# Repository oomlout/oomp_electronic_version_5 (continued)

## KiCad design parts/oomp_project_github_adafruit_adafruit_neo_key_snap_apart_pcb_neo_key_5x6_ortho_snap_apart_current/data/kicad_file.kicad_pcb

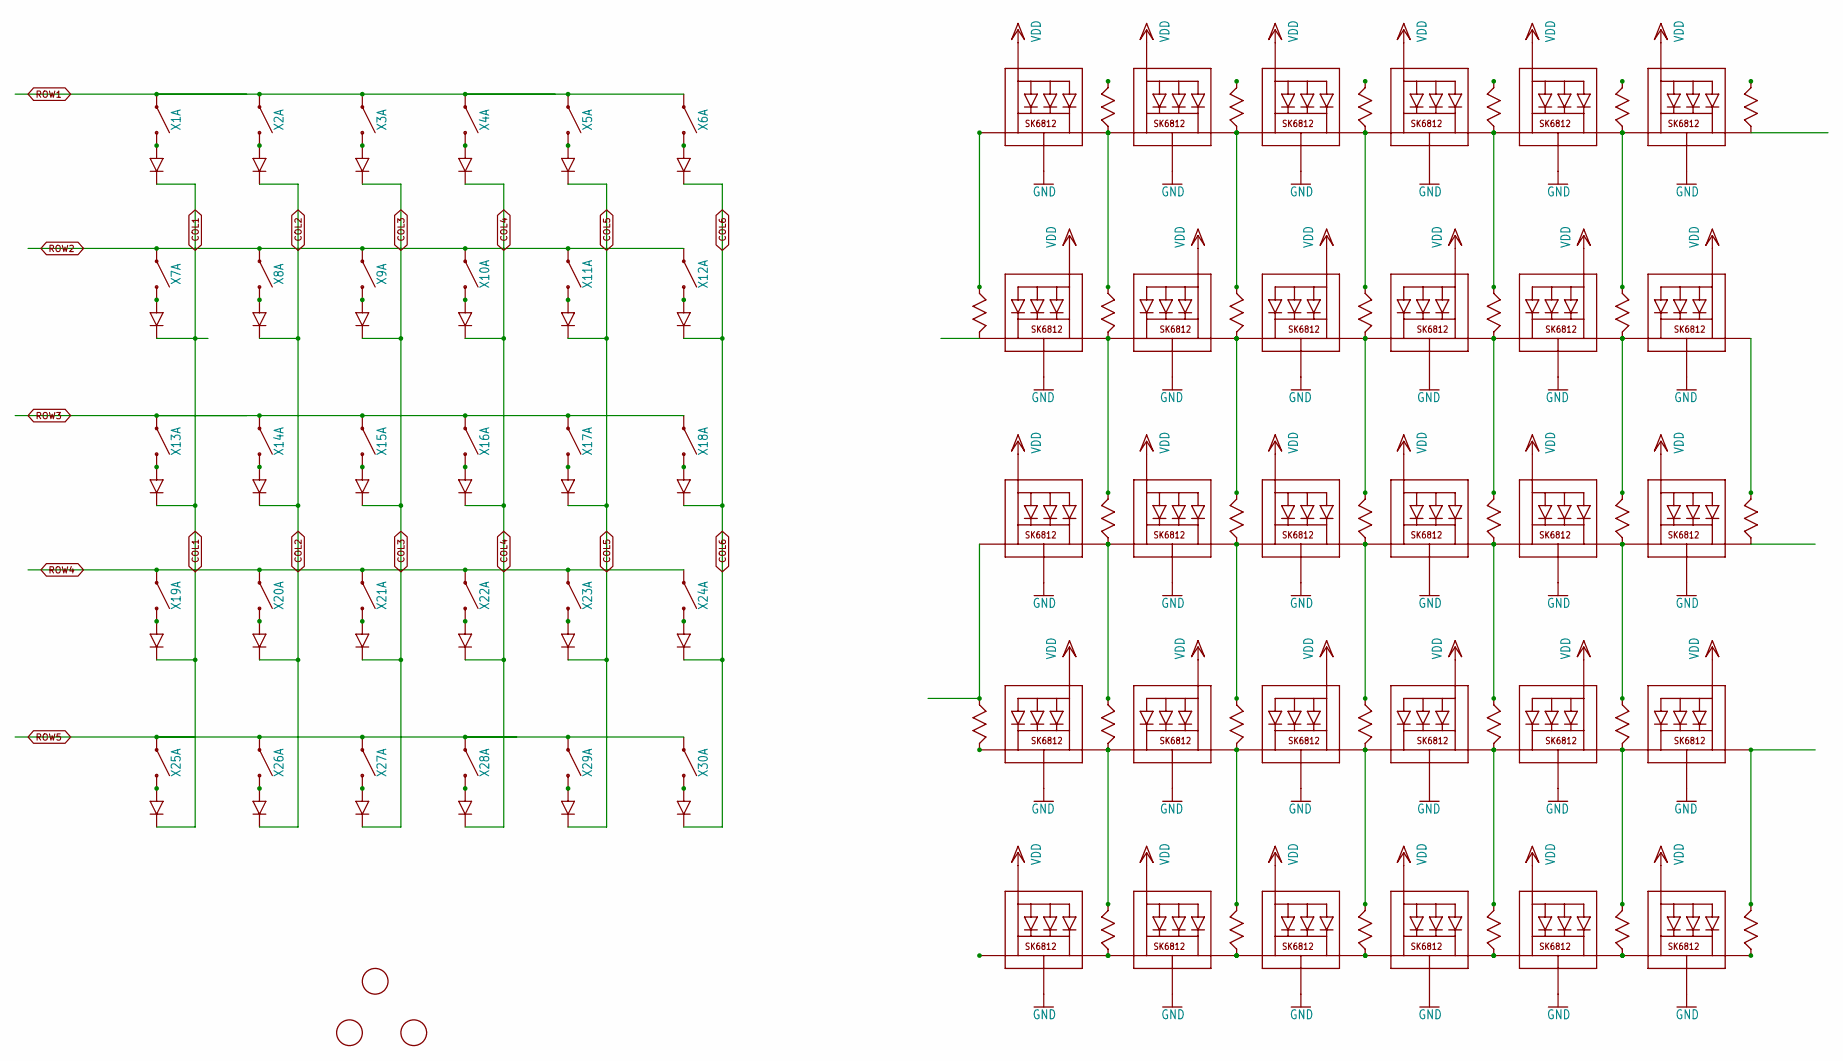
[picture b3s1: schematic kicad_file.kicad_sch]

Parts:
U$1, U$2, U$3: FIDUCIAL; FIDUCIAL_1MM
X1, X2, X3, X4, X5, X6, X13, X14, X15, X16, X17, X18, X25, X26, X27, X28, X29, X30: KAILH_SOCKET_TILE
X7, X8, X9, X10, X11, X12, X19, X20, X21, X22, X23, X24: KAILH_SOCKET_TILE_REVERSE; KAILH_SOCKET_TILE_REV

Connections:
COL1: X1.C (SW_C), X1.C1 (SW_C), X1.C2 (SW_C), X7.C (SW_C), X7.C1 (SW_C), X7.C2 (SW_C), X13.C (SW_C), X13.C1 (SW_C), X13.C2 (SW_C), X19.C (SW_C), X19.C1 (SW_C), X19.C2 (SW_C), X25.C (SW_C), X25.C1 (SW_C), X25.C2 (SW_C)
COL2: X2.C (SW_C), X2.C1 (SW_C), X2.C2 (SW_C), X8.C (SW_C), X8.C1 (SW_C), X8.C2 (SW_C), X14.C (SW_C), X14.C1 (SW_C), X14.C2 (SW_C), X20.C (SW_C), X20.C1 (SW_C), X20.C2 (SW_C), X26.C (SW_C), X26.C1 (SW_C), X26.C2 (SW_C)
COL3: X3.C (SW_C), X3.C1 (SW_C), X3.C2 (SW_C), X9.C (SW_C), X9.C1 (SW_C), X9.C2 (SW_C), X15.C (SW_C), X15.C1 (SW_C), X15.C2 (SW_C), X21.C (SW_C), X21.C1 (SW_C), X21.C2 (SW_C), X27.C (SW_C), X27.C1 (SW_C), X27.C2 (SW_C)
COL4: X4.C (SW_C), X4.C1 (SW_C), X4.C2 (SW_C), X10.C (SW_C), X10.C1 (SW_C), X10.C2 (SW_C), X16.C (SW_C), X16.C1 (SW_C), X16.C2 (SW_C), X22.C (SW_C), X22.C1 (SW_C), X22.C2 (SW_C), X28.C (SW_C), X28.C1 (SW_C), X28.C2 (SW_C)
COL5: X5.C (SW_C), X5.C1 (SW_C), X5.C2 (SW_C), X11.C (SW_C), X11.C1 (SW_C), X11.C2 (SW_C), X17.C (SW_C), X17.C1 (SW_C), X17.C2 (SW_C), X23.C (SW_C), X23.C1 (SW_C), X23.C2 (SW_C), X29.C (SW_C), X29.C1 (SW_C), X29.C2 (SW_C)
COL6: X6.C (SW_C), X6.C1 (SW_C), X6.C2 (SW_C), X12.C (SW_C), X12.C1 (SW_C), X12.C2 (SW_C), X18.C (SW_C), X18.C1 (SW_C), X18.C2 (SW_C), X24.C (SW_C), X24.C1 (SW_C), X24.C2 (SW_C), X30.C (SW_C), X30.C1 (SW_C), X30.C2 (SW_C)
GND: X1.3-GND (GND), X1.C- (GND), X1.GND1 (GND), X1.GND2 (GND), X2.3-GND (GND), X2.C- (GND), X2.GND1 (GND), X2.GND2 (GND), X3.3-GND (GND), X3.C- (GND), X3.GND1 (GND), X3.GND2 (GND), X4.3-GND (GND), X4.C- (GND), X4.GND1 (GND), X4.GND2 (GND), X5.3-GND (GND), X5.C- (GND), X5.GND1 (GND), X5.GND2 (GND), X6.3-GND (GND), X6.C- (GND), X6.GND1 (GND), X6.GND2 (GND), X7.3-GND (GND), X7.C- (GND), X7.GND1 (GND), X7.GND2 (GND), X8.3-GND (GND), X8.C- (GND), X8.GND1 (GND), X8.GND2 (GND), X9.3-GND (GND), X9.C- (GND), X9.GND1 (GND), X9.GND2 (GND), X10.3-GND (GND), X10.C- (GND), X10.GND1 (GND), X10.GND2 (GND), X11.3-GND (GND), X11.C- (GND), X11.GND1 (GND), X11.GND2 (GND), X12.3-GND (GND), X12.C- (GND), X12.GND1 (GND), X12.GND2 (GND), X13.3-GND (GND), X13.C- (GND), X13.GND1 (GND), X13.GND2 (GND), X14.3-GND (GND), X14.C- (GND), X14.GND1 (GND), X14.GND2 (GND), X15.3-GND (GND), X15.C- (GND), X15.GND1 (GND), X15.GND2 (GND), X16.3-GND (GND), X16.C- (GND), X16.GND1 (GND), X16.GND2 (GND), X17.3-GND (GND), X17.C- (GND), X17.GND1 (GND), X17.GND2 (GND), X18.3-GND (GND), X18.C- (GND), X18.GND1 (GND), X18.GND2 (GND), X19.3-GND (GND), X19.C- (GND), X19.GND1 (GND), X19.GND2 (GND), X20.3-GND (GND), X20.C- (GND), X20.GND1 (GND), X20.GND2 (GND), X21.3-GND (GND), X21.C- (GND), X21.GND1 (GND), X21.GND2 (GND), X22.3-GND (GND), X22.C- (GND), X22.GND1 (GND), X22.GND2 (GND), X23.3-GND (GND), X23.C- (GND), X23.GND1 (GND), X23.GND2 (GND), X24.3-GND (GND), X24.C- (GND), X24.GND1 (GND), X24.GND2 (GND), X25.3-GND (GND), X25.C- (GND), X25.GND1 (GND), X25.GND2 (GND), X26.3-GND (GND), X26.C- (GND), X26.GND1 (GND), X26.GND2 (GND), X27.3-GND (GND), X27.C- (GND), X27.GND1 (GND), X27.GND2 (GND), X28.3-GND (GND), X28.C- (GND), X28.GND1 (GND), X28.GND2 (GND), X29.3-GND (GND), X29.C- (GND), X29.GND1 (GND), X29.GND2 (GND), X30.3-GND (GND), X30.C- (GND), X30.GND1 (GND), X30.GND2 (GND)
unnamed: X1.4-DIN (DI), X1.DIN (DI), X1.DIN1 (DI), X2.2-DOUT (DO), X2.DOUT (DO), X2.DOUT1 (DO), X8.DIN_C (DI1), X8.DIN_C1 (DI1)
unnamed: X1.D+ (DA), X1.DA
unnamed: X1.DIN_C (DI1), X1.DIN_C1 (DI1)
unnamed: X2.D+ (DA), X2.DA
unnamed: X4.D+ (DA), X4.DA
unnamed: X1.2-DOUT (DO), X1.DOUT (DO), X1.DOUT1 (DO), X7.DIN_C (DI1), X7.DIN_C1 (DI1)
unnamed: X7.D+ (DA), X7.DA
unnamed: X2.DIN_C (DI1), X2.DIN_C1 (DI1)
unnamed: X3.D+ (DA), X3.DA
unnamed: X2.4-DIN (DI), X2.DIN (DI), X2.DIN1 (DI), X3.2-DOUT (DO), X3.DOUT (DO), X3.DOUT1 (DO), X9.DIN_C (DI1), X9.DIN_C1 (DI1)
unnamed: X3.4-DIN (DI), X3.DIN (DI), X3.DIN1 (DI), X4.2-DOUT (DO), X4.DOUT (DO), X4.DOUT1 (DO), X10.DIN_C (DI1), X10.DIN_C1 (DI1)
unnamed: X3.DIN_C (DI1), X3.DIN_C1 (DI1)
unnamed: X4.4-DIN (DI), X4.DIN (DI), X4.DIN1 (DI), X5.2-DOUT (DO), X5.DOUT (DO), X5.DOUT1 (DO), X11.DIN_C (DI1), X11.DIN_C1 (DI1)
unnamed: X4.DIN_C (DI1), X4.DIN_C1 (DI1)
unnamed: X6.D+ (DA), X6.DA
unnamed: X5.4-DIN (DI), X5.DIN (DI), X5.DIN1 (DI), X6.2-DOUT (DO), X6.DOUT (DO), X6.DOUT1 (DO), X12.DIN_C (DI1), X12.DIN_C1 (DI1)
unnamed: X12.2-DOUT (DO), X12.DOUT (DO), X12.DOUT1 (DO), X18.DIN_C (DI1), X18.DIN_C1 (DI1)
unnamed: X6.DIN_C (DI1), X6.DIN_C1 (DI1)
unnamed: X5.D+ (DA), X5.DA
unnamed: X5.DIN_C (DI1), X5.DIN_C1 (DI1)
unnamed: X6.4-DIN (DI), X6.DIN (DI), X6.DIN1 (DI)
unnamed: X13.D+ (DA), X13.DA
unnamed: X8.D+ (DA), X8.DA
unnamed: X8.2-DOUT (DO), X8.DOUT (DO), X8.DOUT1 (DO), X9.4-DIN (DI), X9.DIN (DI), X9.DIN1 (DI), X14.DIN_C (DI1), X14.DIN_C1 (DI1)
unnamed: X13.2-DOUT (DO), X13.DOUT (DO), X13.DOUT1 (DO), X19.DIN_C (DI1), X19.DIN_C1 (DI1)
unnamed: X9.D+ (DA), X9.DA
unnamed: X9.2-DOUT (DO), X9.DOUT (DO), X9.DOUT1 (DO), X10.4-DIN (DI), X10.DIN (DI), X10.DIN1 (DI), X15.DIN_C (DI1), X15.DIN_C1 (DI1)
unnamed: X13.4-DIN (DI), X13.DIN (DI), X13.DIN1 (DI), X14.2-DOUT (DO), X14.DOUT (DO), X14.DOUT1 (DO), X20.DIN_C (DI1), X20.DIN_C1 (DI1)
unnamed: X10.D+ (DA), X10.DA
unnamed: X10.2-DOUT (DO), X10.DOUT (DO), X10.DOUT1 (DO), X11.4-DIN (DI), X11.DIN (DI), X11.DIN1 (DI), X16.DIN_C (DI1), X16.DIN_C1 (DI1)
unnamed: X7.2-DOUT (DO), X7.DOUT (DO), X7.DOUT1 (DO), X8.4-DIN (DI), X8.DIN (DI), X8.DIN1 (DI), X13.DIN_C (DI1), X13.DIN_C1 (DI1)
unnamed: X11.D+ (DA), X11.DA
unnamed: X11.2-DOUT (DO), X11.DOUT (DO), X11.DOUT1 (DO), X12.4-DIN (DI), X12.DIN (DI), X12.DIN1 (DI), X17.DIN_C (DI1), X17.DIN_C1 (DI1)
unnamed: X15.D+ (DA), X15.DA
unnamed: X12.D+ (DA), X12.DA
unnamed: X14.4-DIN (DI), X14.DIN (DI), X14.DIN1 (DI), X15.2-DOUT (DO), X15.DOUT (DO), X15.DOUT1 (DO), X21.DIN_C (DI1), X21.DIN_C1 (DI1)
unnamed: X7.4-DIN (DI), X7.DIN (DI), X7.DIN1 (DI)
unnamed: X14.D+ (DA), X14.DA
unnamed: X25.D+ (DA), X25.DA
unnamed: X16.D+ (DA), X16.DA
unnamed: X16.4-DIN (DI), X16.DIN (DI), X16.DIN1 (DI), X17.2-DOUT (DO), X17.DOUT (DO), X17.DOUT1 (DO), X23.DIN_C (DI1), X23.DIN_C1 (DI1)
unnamed: X25.2-DOUT (DO), X25.DOUT (DO), X25.DOUT1 (DO)
unnamed: X18.D+ (DA), X18.DA
unnamed: X17.4-DIN (DI), X17.DIN (DI), X17.DIN1 (DI), X18.2-DOUT (DO), X18.DOUT (DO), X18.DOUT1 (DO), X24.DIN_C (DI1), X24.DIN_C1 (DI1)
unnamed: X18.4-DIN (DI), X18.DIN (DI), X18.DIN1 (DI)
unnamed: X25.4-DIN (DI), X25.DIN (DI), X25.DIN1 (DI), X26.2-DOUT (DO), X26.DOUT (DO), X26.DOUT1 (DO)
unnamed: X17.D+ (DA), X17.DA
unnamed: X15.4-DIN (DI), X15.DIN (DI), X15.DIN1 (DI), X16.2-DOUT (DO), X16.DOUT (DO), X16.DOUT1 (DO), X22.DIN_C (DI1), X22.DIN_C1 (DI1)
unnamed: X19.D+ (DA), X19.DA
unnamed: X19.2-DOUT (DO), X19.DOUT (DO), X19.DOUT1 (DO), X20.4-DIN (DI), X20.DIN (DI), X20.DIN1 (DI), X25.DIN_C (DI1), X25.DIN_C1 (DI1)
unnamed: X19.4-DIN (DI), X19.DIN (DI), X19.DIN1 (DI)
unnamed: X20.D+ (DA), X20.DA
unnamed: X20.2-DOUT (DO), X20.DOUT (DO), X20.DOUT1 (DO), X21.4-DIN (DI), X21.DIN (DI), X21.DIN1 (DI), X26.DIN_C (DI1), X26.DIN_C1 (DI1)
unnamed: X21.D+ (DA), X21.DA
unnamed: X22.D+ (DA), X22.DA
unnamed: X22.2-DOUT (DO), X22.DOUT (DO), X22.DOUT1 (DO), X23.4-DIN (DI), X23.DIN (DI), X23.DIN1 (DI), X28.DIN_C (DI1), X28.DIN_C1 (DI1)
unnamed: X23.D+ (DA), X23.DA
unnamed: X23.2-DOUT (DO), X23.DOUT (DO), X23.DOUT1 (DO), X24.4-DIN (DI), X24.DIN (DI), X24.DIN1 (DI), X29.DIN_C (DI1), X29.DIN_C1 (DI1)
unnamed: X24.D+ (DA), X24.DA
unnamed: X27.D+ (DA), X27.DA
unnamed: X26.4-DIN (DI), X26.DIN (DI), X26.DIN1 (DI), X27.2-DOUT (DO), X27.DOUT (DO), X27.DOUT1 (DO)
unnamed: X21.2-DOUT (DO), X21.DOUT (DO), X21.DOUT1 (DO), X22.4-DIN (DI), X22.DIN (DI), X22.DIN1 (DI), X27.DIN_C (DI1), X27.DIN_C1 (DI1)
unnamed: X26.D+ (DA), X26.DA
unnamed: X28.D+ (DA), X28.DA
unnamed: X28.4-DIN (DI), X28.DIN (DI), X28.DIN1 (DI), X29.2-DOUT (DO), X29.DOUT (DO), X29.DOUT1 (DO)
unnamed: X30.D+ (DA), X30.DA
unnamed: X29.4-DIN (DI), X29.DIN (DI), X29.DIN1 (DI), X30.2-DOUT (DO), X30.DOUT (DO), X30.DOUT1 (DO)
unnamed: X30.4-DIN (DI), X30.DIN (DI), X30.DIN1 (DI)
unnamed: X24.2-DOUT (DO), X24.DOUT (DO), X24.DOUT1 (DO), X30.DIN_C (DI1), X30.DIN_C1 (DI1)
unnamed: X29.D+ (DA), X29.DA
unnamed: X27.4-DIN (DI), X27.DIN (DI), X27.DIN1 (DI), X28.2-DOUT (DO), X28.DOUT (DO), X28.DOUT1 (DO)
ROW1: X1.A (SW_A), X1.A1 (SW_A), X1.A2 (SW_A), X2.A (SW_A), X2.A1 (SW_A), X2.A2 (SW_A), X3.A (SW_A), X3.A1 (SW_A), X3.A2 (SW_A), X4.A (SW_A), X4.A1 (SW_A), X4.A2 (SW_A), X5.A (SW_A), X5.A1 (SW_A), X5.A2 (SW_A), X6.A (SW_A), X6.A1 (SW_A), X6.A2 (SW_A)
ROW2: X7.A (SW_A), X7.A1 (SW_A), X7.A2 (SW_A), X8.A (SW_A), X8.A1 (SW_A), X8.A2 (SW_A), X9.A (SW_A), X9.A1 (SW_A), X9.A2 (SW_A), X10.A (SW_A), X10.A1 (SW_A), X10.A2 (SW_A), X11.A (SW_A), X11.A1 (SW_A), X11.A2 (SW_A), X12.A (SW_A), X12.A1 (SW_A), X12.A2 (SW_A)
ROW3: X13.A (SW_A), X13.A1 (SW_A), X13.A2 (SW_A), X14.A (SW_A), X14.A1 (SW_A), X14.A2 (SW_A), X15.A (SW_A), X15.A1 (SW_A), X15.A2 (SW_A), X16.A (SW_A), X16.A1 (SW_A), X16.A2 (SW_A), X17.A (SW_A), X17.A1 (SW_A), X17.A2 (SW_A), X18.A (SW_A), X18.A1 (SW_A), X18.A2 (SW_A)
ROW4: X19.A (SW_A), X19.A1 (SW_A), X19.A2 (SW_A), X20.A (SW_A), X20.A1 (SW_A), X20.A2 (SW_A), X21.A (SW_A), X21.A1 (SW_A), X21.A2 (SW_A), X22.A (SW_A), X22.A1 (SW_A), X22.A2 (SW_A), X23.A (SW_A), X23.A1 (SW_A), X23.A2 (SW_A), X24.A (SW_A), X24.A1 (SW_A), X24.A2 (SW_A)
ROW5: X25.A (SW_A), X25.A1 (SW_A), X25.A2 (SW_A), X26.A (SW_A), X26.A1 (SW_A), X26.A2 (SW_A), X27.A (SW_A), X27.A1 (SW_A), X27.A2 (SW_A), X28.A (SW_A), X28.A1 (SW_A), X28.A2 (SW_A), X29.A (SW_A), X29.A1 (SW_A), X29.A2 (SW_A), X30.A (SW_A), X30.A1 (SW_A), X30.A2 (SW_A)
VDD: X1.1-VDD (VDD), X1.C+ (VDD), X1.VDD1 (VDD), X1.VDD2 (VDD), X2.1-VDD (VDD), X2.C+ (VDD), X2.VDD1 (VDD), X2.VDD2 (VDD), X3.1-VDD (VDD), X3.C+ (VDD), X3.VDD1 (VDD), X3.VDD2 (VDD), X4.1-VDD (VDD), X4.C+ (VDD), X4.VDD1 (VDD), X4.VDD2 (VDD), X5.1-VDD (VDD), X5.C+ (VDD), X5.VDD1 (VDD), X5.VDD2 (VDD), X6.1-VDD (VDD), X6.C+ (VDD), X6.VDD1 (VDD), X6.VDD2 (VDD), X7.1-VDD (VDD), X7.C+ (VDD), X7.VDD1 (VDD), X7.VDD2 (VDD), X8.1-VDD (VDD), X8.C+ (VDD), X8.VDD1 (VDD), X8.VDD2 (VDD), X9.1-VDD (VDD), X9.C+ (VDD), X9.VDD1 (VDD), X9.VDD2 (VDD), X10.1-VDD (VDD), X10.C+ (VDD), X10.VDD1 (VDD), X10.VDD2 (VDD), X11.1-VDD (VDD), X11.C+ (VDD), X11.VDD1 (VDD), X11.VDD2 (VDD), X12.1-VDD (VDD), X12.C+ (VDD), X12.VDD1 (VDD), X12.VDD2 (VDD), X13.1-VDD (VDD), X13.C+ (VDD), X13.VDD1 (VDD), X13.VDD2 (VDD), X14.1-VDD (VDD), X14.C+ (VDD), X14.VDD1 (VDD), X14.VDD2 (VDD), X15.1-VDD (VDD), X15.C+ (VDD), X15.VDD1 (VDD), X15.VDD2 (VDD), X16.1-VDD (VDD), X16.C+ (VDD), X16.VDD1 (VDD), X16.VDD2 (VDD), X17.1-VDD (VDD), X17.C+ (VDD), X17.VDD1 (VDD), X17.VDD2 (VDD), X18.1-VDD (VDD), X18.C+ (VDD), X18.VDD1 (VDD), X18.VDD2 (VDD), X19.1-VDD (VDD), X19.C+ (VDD), X19.VDD1 (VDD), X19.VDD2 (VDD), X20.1-VDD (VDD), X20.C+ (VDD), X20.VDD1 (VDD), X20.VDD2 (VDD), X21.1-VDD (VDD), X21.C+ (VDD), X21.VDD1 (VDD), X21.VDD2 (VDD), X22.1-VDD (VDD), X22.C+ (VDD), X22.VDD1 (VDD), X22.VDD2 (VDD), X23.1-VDD (VDD), X23.C+ (VDD), X23.VDD1 (VDD), X23.VDD2 (VDD), X24.1-VDD (VDD), X24.C+ (VDD), X24.VDD1 (VDD), X24.VDD2 (VDD), X25.1-VDD (VDD), X25.C+ (VDD), X25.VDD1 (VDD), X25.VDD2 (VDD), X26.1-VDD (VDD), X26.C+ (VDD), X26.VDD1 (VDD), X26.VDD2 (VDD), X27.1-VDD (VDD), X27.C+ (VDD), X27.VDD1 (VDD), X27.VDD2 (VDD), X28.1-VDD (VDD), X28.C+ (VDD), X28.VDD1 (VDD), X28.VDD2 (VDD), X29.1-VDD (VDD), X29.C+ (VDD), X29.VDD1 (VDD), X29.VDD2 (VDD), X30.1-VDD (VDD), X30.C+ (VDD), X30.VDD1 (VDD), X30.VDD2 (VDD)

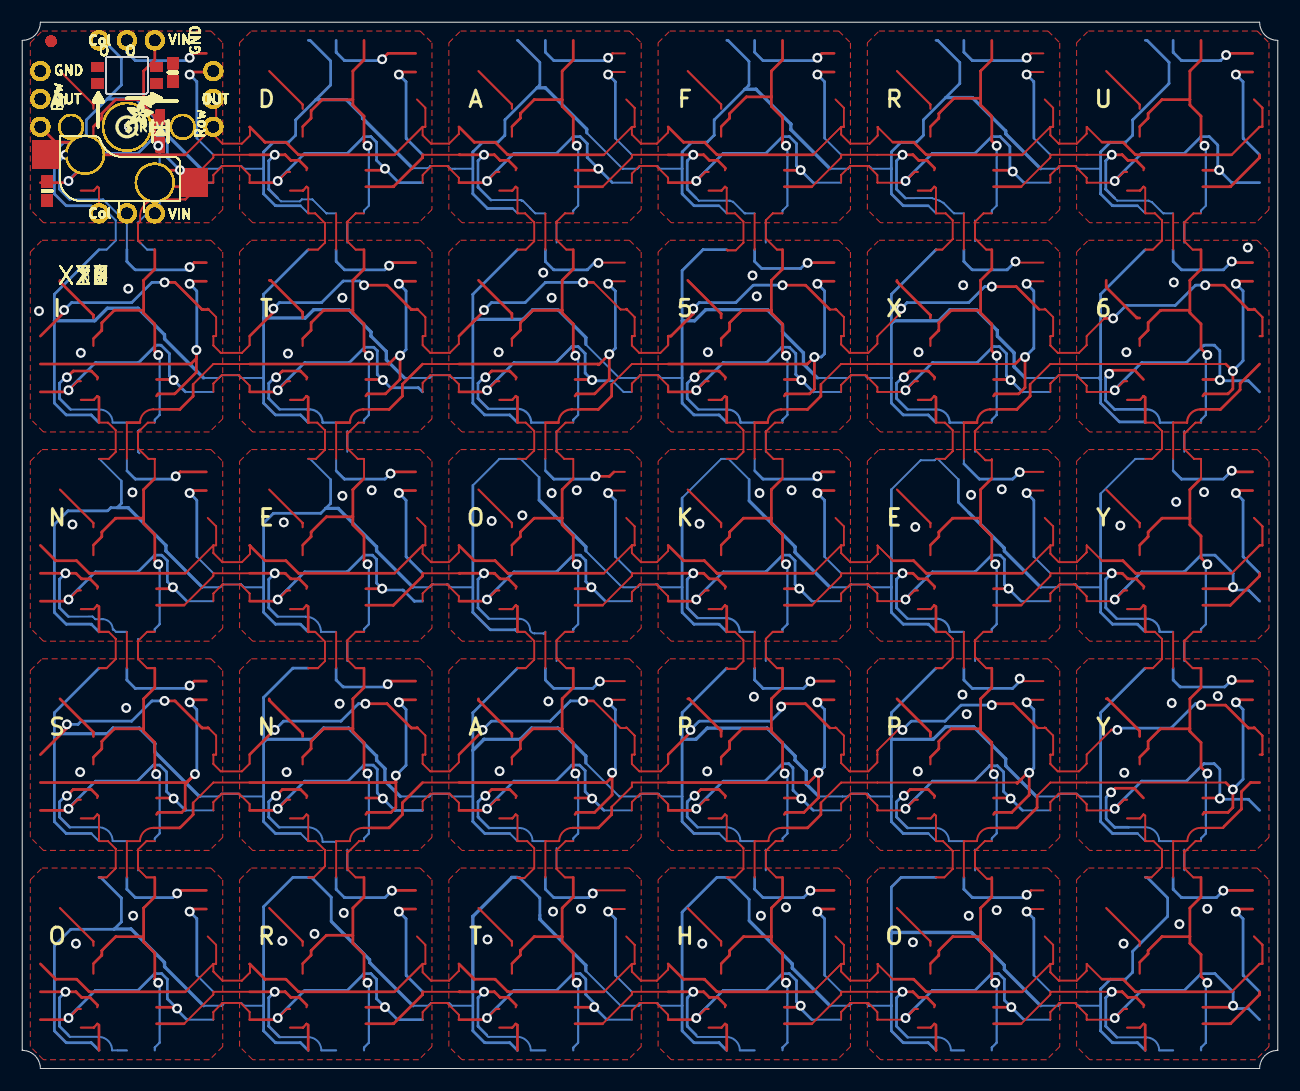
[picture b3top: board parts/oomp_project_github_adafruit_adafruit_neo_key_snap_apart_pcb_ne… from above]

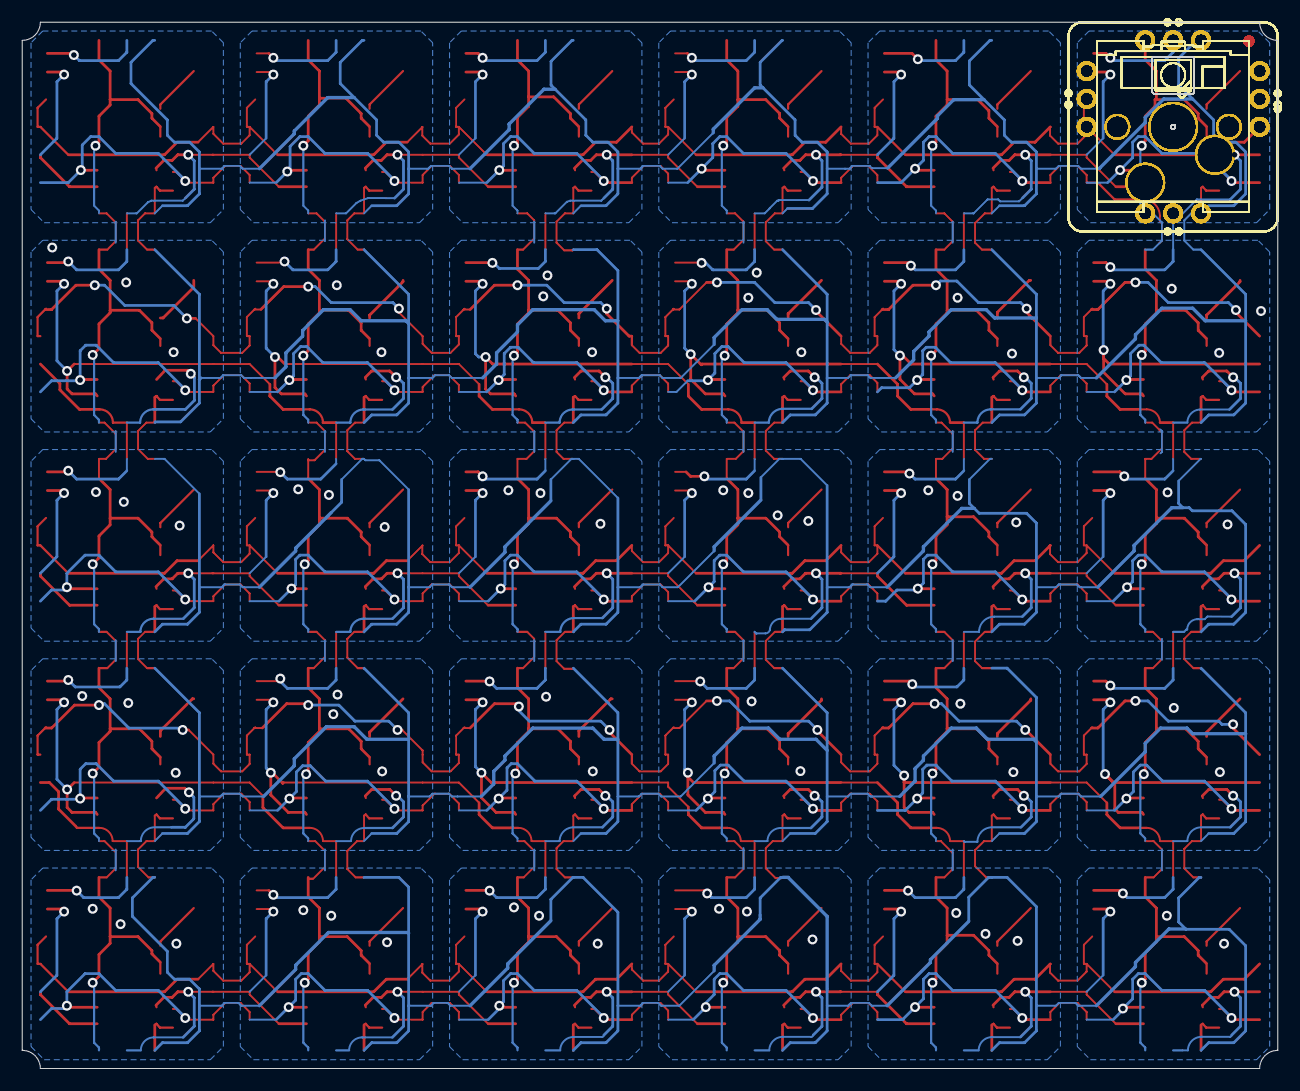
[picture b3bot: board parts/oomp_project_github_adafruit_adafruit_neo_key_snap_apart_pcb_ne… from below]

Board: 2 copper layers, 114.3 x 95.2 mm, 134 parts (30 on the bottom side), 84 nets.

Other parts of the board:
U$4, U$5: ADAFRUIT_2.5MM
U$6: PCBFEAT-REV-040
UNK_HOLE_0: dummyfp0
UNK_HOLE_1: dummyfp1
UNK_HOLE_2: dummyfp2
UNK_HOLE_3: dummyfp3
UNK_HOLE_4: dummyfp4
UNK_HOLE_5: dummyfp5
UNK_HOLE_6: dummyfp6
UNK_HOLE_7: dummyfp7
UNK_HOLE_8: dummyfp8
UNK_HOLE_9: dummyfp9
UNK_HOLE_10: dummyfp10
UNK_HOLE_11: dummyfp11
UNK_HOLE_12: dummyfp12
UNK_HOLE_13: dummyfp13
UNK_HOLE_14: dummyfp14
UNK_HOLE_15: dummyfp15
UNK_HOLE_16: dummyfp16
UNK_HOLE_17: dummyfp17
UNK_HOLE_18: dummyfp18
UNK_HOLE_19: dummyfp19
UNK_HOLE_20: dummyfp20
UNK_HOLE_21: dummyfp21
UNK_HOLE_22: dummyfp22
UNK_HOLE_23: dummyfp23
UNK_HOLE_24: dummyfp24
UNK_HOLE_25: dummyfp25
UNK_HOLE_26: dummyfp26
UNK_HOLE_27: dummyfp27
UNK_HOLE_28: dummyfp28
UNK_HOLE_29: dummyfp29
UNK_HOLE_30: dummyfp30
UNK_HOLE_31: dummyfp31
UNK_HOLE_32: dummyfp32
UNK_HOLE_33: dummyfp33
UNK_HOLE_34: dummyfp34
UNK_HOLE_35: dummyfp35
UNK_HOLE_36: dummyfp36
UNK_HOLE_37: dummyfp37
UNK_HOLE_38: dummyfp38
UNK_HOLE_39: dummyfp39
UNK_HOLE_40: dummyfp40
UNK_HOLE_41: dummyfp41
UNK_HOLE_42: dummyfp42
UNK_HOLE_43: dummyfp43
UNK_HOLE_44: dummyfp44
UNK_HOLE_45: dummyfp45
UNK_HOLE_46: dummyfp46
UNK_HOLE_47: dummyfp47
UNK_HOLE_48: dummyfp48
UNK_HOLE_49: dummyfp49
UNK_HOLE_50: dummyfp50
UNK_HOLE_51: dummyfp51
UNK_HOLE_52: dummyfp52
UNK_HOLE_53: dummyfp53
UNK_HOLE_54: dummyfp54
UNK_HOLE_55: dummyfp55
UNK_HOLE_56: dummyfp56
UNK_HOLE_57: dummyfp57
UNK_HOLE_58: dummyfp58
UNK_HOLE_59: dummyfp59
UNK_HOLE_60: dummyfp60
UNK_HOLE_61: dummyfp61
UNK_HOLE_62: dummyfp62
UNK_HOLE_63: dummyfp63
UNK_HOLE_64: dummyfp64
UNK_HOLE_65: dummyfp65
UNK_HOLE_66: dummyfp66
UNK_HOLE_67: dummyfp67
UNK_HOLE_68: dummyfp68
UNK_HOLE_69: dummyfp69
UNK_HOLE_70: dummyfp70
UNK_HOLE_71: dummyfp71
UNK_HOLE_72: dummyfp72
UNK_HOLE_73: dummyfp73
UNK_HOLE_74: dummyfp74
UNK_HOLE_75: dummyfp75
UNK_HOLE_76: dummyfp76
UNK_HOLE_77: dummyfp77
UNK_HOLE_78: dummyfp78
UNK_HOLE_79: dummyfp79
UNK_HOLE_80: dummyfp80
UNK_HOLE_81: dummyfp81
UNK_HOLE_82: dummyfp82
UNK_HOLE_83: dummyfp83
UNK_HOLE_84: dummyfp84
UNK_HOLE_85: dummyfp85
UNK_HOLE_86: dummyfp86
UNK_HOLE_87: dummyfp87
UNK_HOLE_88: dummyfp88
UNK_HOLE_89: dummyfp89
UNK_HOLE_90: dummyfp90
UNK_HOLE_91: dummyfp91
UNK_HOLE_92: dummyfp92
UNK_HOLE_93: dummyfp93
UNK_HOLE_94: dummyfp94
UNK_HOLE_95: dummyfp95
UNK_HOLE_96: dummyfp96
UNK_HOLE_97: dummyfp97

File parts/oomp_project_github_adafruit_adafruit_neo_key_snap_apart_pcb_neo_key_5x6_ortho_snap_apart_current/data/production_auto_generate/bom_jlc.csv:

Comment,Designator,Footprint,LCSC Part #
,"U$4,U$5",NeoKey 5x6 Ortho Snap-Apart-import-fps:ADAFRUIT_2.5MM,
,U$6,NeoKey 5x6 Ortho Snap-Apart-import-fps:PCBFEAT-REV-040,
FIDUCIAL,"U$1,U$2,U$3",NeoKey 5x6 Ortho Snap-Apart-import-fps:FIDUCIAL_1MM,
KAILH_SOCKET_TILE,"X1,X2,X3,X4,X5,X6,X13,X14,X15,X16,X17,X18,X25,X26,X27,X28,X29,X30",NeoKey 5x6 Ortho Snap-Apart-import-fps:KAILH_SOCKET_TILE,
KAILH_SOCKET_TILE_REVERSE,"X7,X8,X9,X10,X11,X12,X19,X20,X21,X22,X23,X24",NeoKey 5x6 Ortho Snap-Apart-import-fps:KAILH_SOCKET_TILE_REV,

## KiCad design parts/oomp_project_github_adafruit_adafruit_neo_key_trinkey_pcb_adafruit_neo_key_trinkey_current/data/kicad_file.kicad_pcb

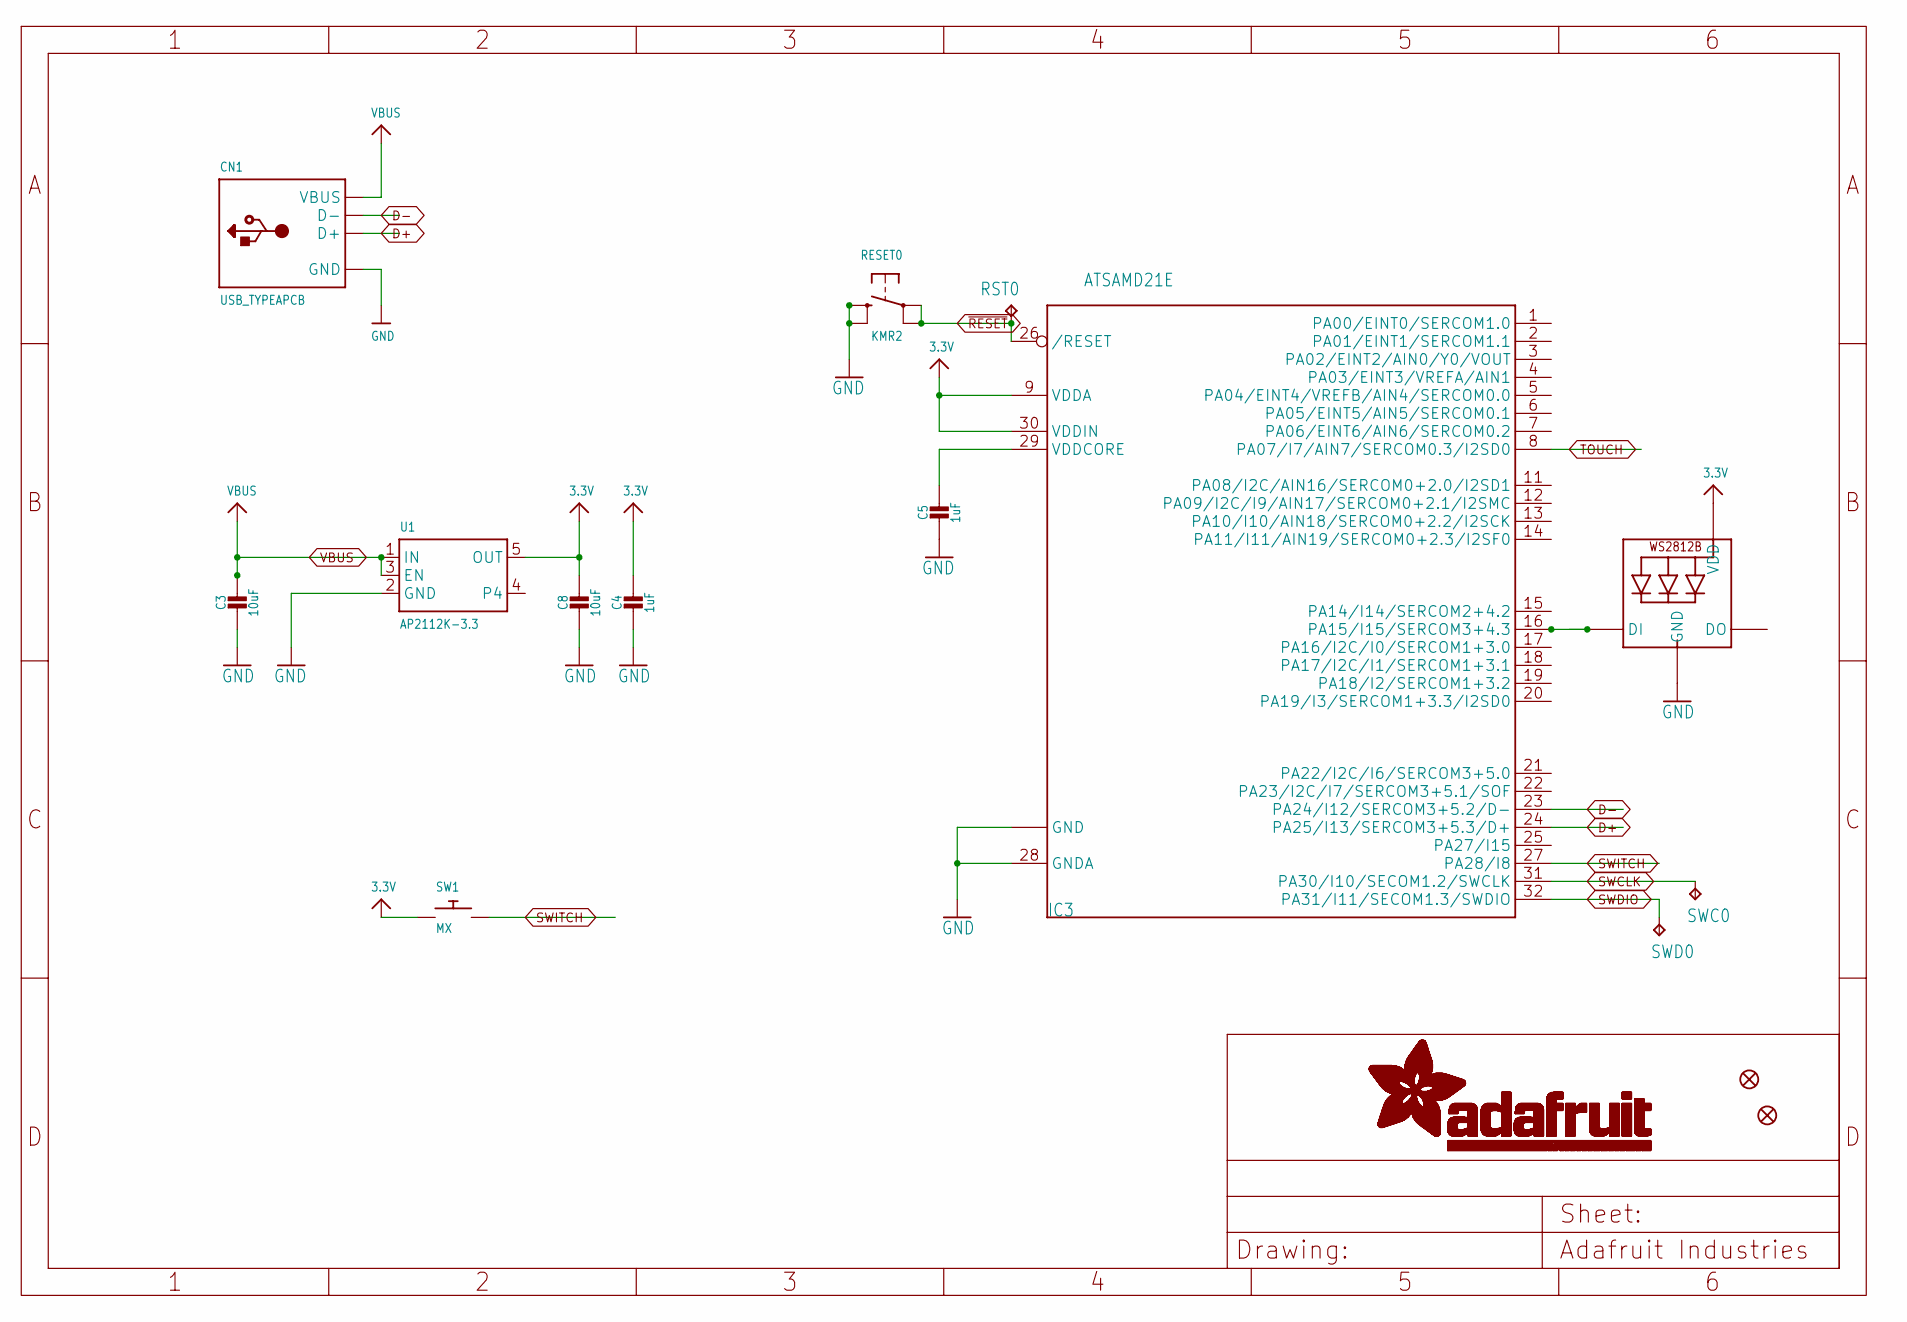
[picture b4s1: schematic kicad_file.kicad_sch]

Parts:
C3, C8: 10uF; 0805-NO
C4, C5: 1uF; 0603-NO
CN1: USB_TYPEAPCB; USBA_PCB
FID1, FID2: FIDUCIAL_1MM
IC3: ATSAMD21E; QFN32_5MM
LED1: WS2812B_SK6812E; NEO3535_REVERSE
RESET0: KMR2; BTN_KMR2_4.6X2.8
RST0: RST; TP16R
SW1: MX; KAILH_BOX_MX_NOSTABILIZERS
SWC0: SWC; TP15R
SWD0: SWD; TP15R
U1: AP2112K-3.3; SOT23-5

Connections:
3.3V: C4.1, C8.1, IC3.9 (VDDA), IC3.30 (VDDIN), LED1.1-VDD (VDD), SW1.1, U1.5 (OUT)
D+: CN1.USB_PLUS (D+), IC3.24 (PA25/I13/SERCOM3+5.3/D+)
D-: CN1.USB_NEG (D-), IC3.23 (PA24/I12/SERCOM3+5.2/D-)
GND: C3.2, C4.2, C5.2, C8.2, CN1.GND, IC3.10 (GND), IC3.28 (GNDA), IC3.33 (GND), LED1.3-GND (GND), RESET0.B (S), RESET0.B' (S1), U1.2 (GND)
unnamed: IC3.16 (PA15/I15/SERCOM3+4.3), LED1.4-DIN (DI)
SWCLK: IC3.31 (PA30/I10/SECOM1.2/SWCLK), SWC0.TP
SWDIO: IC3.32 (PA31/I11/SECOM1.3/SWDIO), SWD0.TP
SWITCH: IC3.27 (PA28/I8), SW1.2
TOUCH: IC3.8 (PA07/I7/AIN7/SERCOM0.3/I2SD0)
VBUS: C3.1, CN1.VCC (VBUS), U1.1 (IN), U1.3 (EN)
VDDCORE1: C5.1, IC3.29 (VDDCORE)
~RESET: IC3.26 (/RESET), RESET0.A, RESET0.A' (P1), RST0.TP

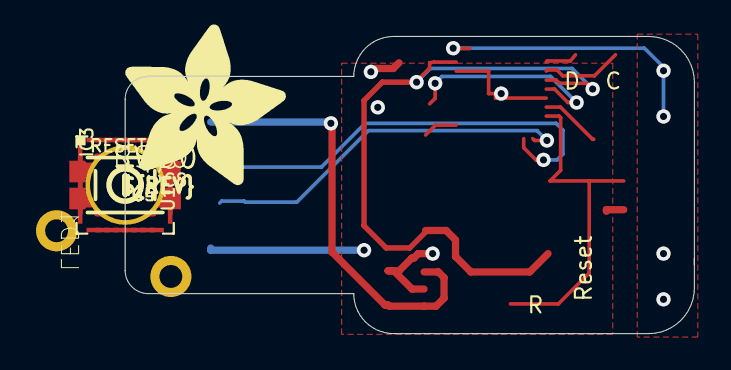
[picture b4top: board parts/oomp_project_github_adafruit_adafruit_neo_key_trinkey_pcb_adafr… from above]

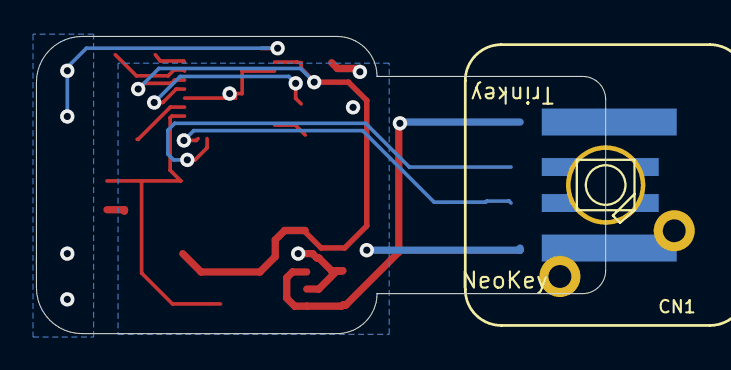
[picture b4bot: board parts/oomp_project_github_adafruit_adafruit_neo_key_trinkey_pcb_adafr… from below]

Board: 2 copper layers, 31.6 x 16.5 mm, 17 parts (3 on the bottom side), 11 nets.

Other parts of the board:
U$6: ADAFRUIT_9MM
U$8: PCBFEAT-REV-040

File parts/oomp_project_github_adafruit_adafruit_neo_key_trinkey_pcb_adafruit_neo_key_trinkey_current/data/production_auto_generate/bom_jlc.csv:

Comment,Designator,Footprint,LCSC Part #
,U$6,Adafruit NeoKey Trinkey-import-fps:ADAFRUIT_9MM,
,U$8,Adafruit NeoKey Trinkey-import-fps:PCBFEAT-REV-040,
,CN1,Adafruit NeoKey Trinkey-import-fps:USBA_PCB,
10uF,"C3,C8",Adafruit NeoKey Trinkey-import-fps:0805-NO,
1uF,"C4,C5",Adafruit NeoKey Trinkey-import-fps:0603-NO,C5673
AP2112K-3.3,U1,Adafruit NeoKey Trinkey-import-fps:SOT23-5,
ATSAMD21E,IC3,Adafruit NeoKey Trinkey-import-fps:QFN32_5MM,
KMR2,RESET0,Adafruit NeoKey Trinkey-import-fps:BTN_KMR2_4.6X2.8,
MX,SW1,Adafruit NeoKey Trinkey-import-fps:KAILH_BOX_MX_NOSTABILIZERS,
RST,RST0,Adafruit NeoKey Trinkey-import-fps:TP16R,
SWC,SWC0,Adafruit NeoKey Trinkey-import-fps:TP15R,
SWD,SWD0,Adafruit NeoKey Trinkey-import-fps:TP15R,
WS2812B_SK6812E,LED1,Adafruit NeoKey Trinkey-import-fps:NEO3535_REVERSE,
